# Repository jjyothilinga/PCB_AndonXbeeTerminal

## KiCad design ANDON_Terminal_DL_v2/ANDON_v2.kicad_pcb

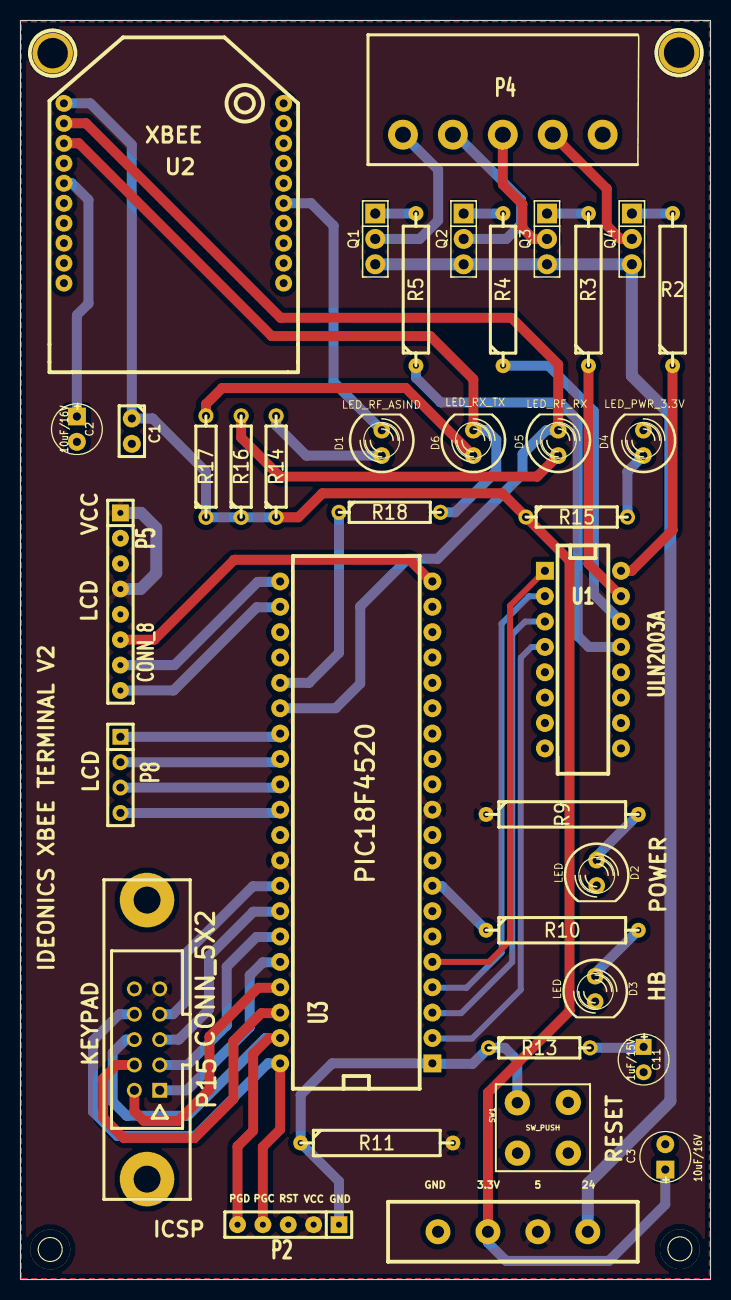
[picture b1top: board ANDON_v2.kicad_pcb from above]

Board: 2 copper layers, 69.1 x 126.1 mm, 36 parts (0 on the bottom side), 49 nets.

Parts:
C1: 0.1uF; C1
C2, C3: 10uF/16V; C1V5
C11: 1uF/15V; Ideonics_Electrolytic_CV5
D1: LED_RF_ASIND; LED-5MM
D2, D3: LED; LED-5MM
D4: LED_PWR_3.3V; LED-5MM
D5: LED_RF_RX; LED-5MM
D6: LED_RX_TX; LED-5MM
P2: PRG_CONN; SIL-5
P4: CONN_5; Ideonics_COMBICON_5
P5: CONN_8; Ideonics_RMC_8
P8: CONN_4; Ideonics_RMC_4Pin
P15: CONN_5X2; he10-10d
Q1, Q2, Q3, Q4: TIP127; Ideonics_TIP127
R2, R3, R4, R5: 2.2K; Ideonics_R
R9, R10: 1K; Ideonics_R
R11: 1M; Ideonics_R
R13: 0; R4
R14, R15, R16, R17: 470; R4
R18: 4.7K; R4
SW1: SW_PUSH; Ideonics_Micro_Switch
U1: ULN2003A; Idenoics_ULN2003
U2: XBEE; XBee-pro
U3: PIC18F4520; DIP-40__600

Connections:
/PGC: P2.5, P15.6, U3.39
/PGD: P2.4, P15.8, U3.40
/RA0: U1.4, U3.2
/RA1: U1.3, U3.3
/RA2: U1.2, U3.4
/RA3: U1.1, U3.5
/RB0: P15.7, U3.33
/RB1: P15.5, U3.34
/RB2: P15.3, U3.35
/RB3: P15.1, U3.36
/RB4: P15.2, U3.37
/RB5: P15.4, U3.38
/RE0: R10.1, U3.8
/RESET: P2.1, R11.1, R13.1, SW1.2, U3.1
/TX: R18.1, U3.25
/ULN1: Q4.1, R2.2
/ULN2: Q3.1, R3.2
/ULN3: Q2.1, R4.2
/ULN4: Q1.1, R5.2
/VCC: P2.2, P5.1, P5.4, P15.9, R9.1, R11.2, U3.11, U3.32
/VCC_3.3V: C1.1, C3.1, R14.1, R15.1, R16.1, R17.1, U2.1
/VCC_24: Q1.3, Q2.3, Q3.3, Q4.3
/XBEE_RX: D5.2, U2.2, U3.26
/XBEE_TX: D6.2, R18.2, U2.3
GND: C1.2, C2.2, C3.2, C11.2, D2.2, D3.2, D4.2, P2.3, P4.5, P5.2, P5.3, P5.5, P15.10, SW1.1, U1.8, U2.10, U3.12, U3.31
unnamed: R5.1, U1.13
unnamed: R4.1, U1.14
unnamed: R3.1, U1.15
unnamed: R2.1, U1.16
unnamed: P5.7, U3.21
unnamed: P8.4, U3.30
unnamed: P8.3, U3.29
unnamed: P8.2, U3.28
unnamed: P8.1, U3.27
unnamed: P5.8, U3.22
unnamed: P5.6, U3.20
unnamed: P4.1, Q1.2
unnamed: P4.3, Q3.2
unnamed: D4.1, R15.2
unnamed: D5.1, R16.2
unnamed: D6.1, R17.2
unnamed: C2.1, U2.5
unnamed: P4.2, Q2.2
unnamed: P4.4, Q4.2
unnamed: C11.1, R13.2
unnamed: D1.1, R14.2
unnamed: D1.2, U2.15
unnamed: D3.1, R10.2
unnamed: D2.1, R9.2

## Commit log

2015-04-22 :circus_tent: Added .gitattributes & .gitignore files
2016-08-15 PIC PROGRAMMING CONNECTOR MODIFICATION
